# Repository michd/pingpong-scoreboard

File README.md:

# Pingpong Scoreboard

This is an electronics hardware and firmware project for a Pingpong scoreboard.

Its user interface consists for a 4-digit 7 segment display, a few LEDs, a button for each side of the table, and a button for the scoreboard.

The scoreboard keeps track of the score within the game, within the set (games won each side since power-up) and of the overall score (games won each side, all time).

## Hardware

Since the program for this is really simple, and there isn't much I/O, an ATTiny84 was chose as the microcontroller, of the Microchip/AVR range. It is programmed via ISP, and I'm programming it using a Waveshare AVRISP MKII.

The display is driven using a Maxim Integrated MAX7219. The few extra indication LEDs are also driven by that, since the chip supports up to 8 digits, and the project only requires 4.

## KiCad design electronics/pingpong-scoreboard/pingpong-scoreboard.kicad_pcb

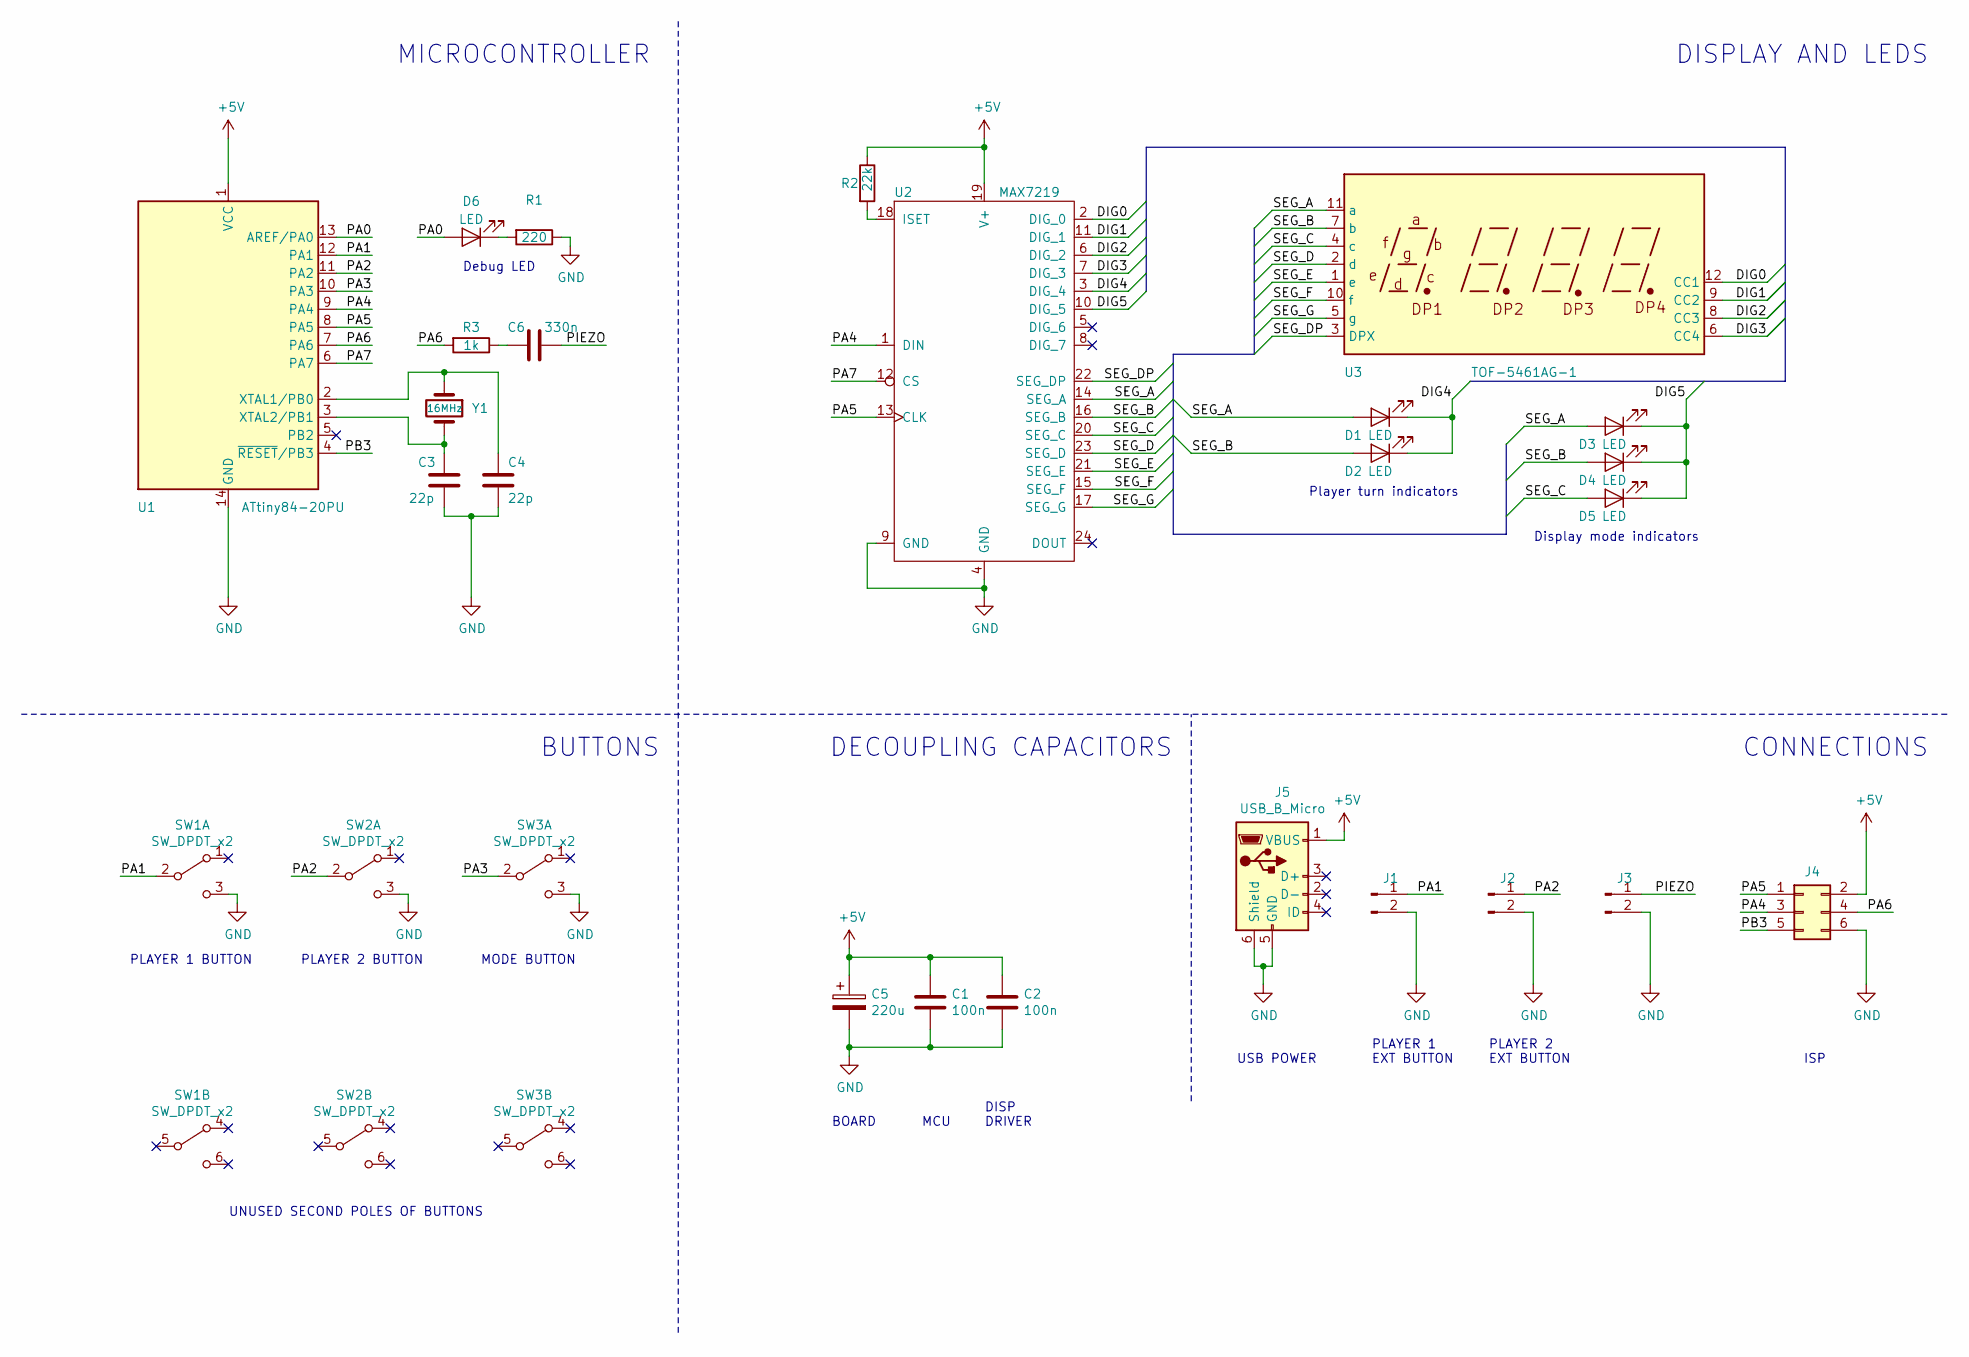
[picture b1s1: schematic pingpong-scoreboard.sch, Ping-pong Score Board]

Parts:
C1, C2: 100n; C_Disc_D4.3mm_W1.9mm_P5.00mm
C3, C4: 22p; C_Disc_D4.3mm_W1.9mm_P5.00mm
C5: 220u; CP_Radial_D6.3mm_P2.50mm
C6: 330n; C_0603_1608Metric
D1, D2: LED; LED_D5.0mm_Clear
D3, D4, D5: LED; LED_D5.0mm
D6: LED; LED_0603_1608Metric
J1, J2, J3: Conn_01x02_Male; PinHeader_1x02_P2.54mm_Horizontal
J4: Conn_02x03_Odd_Even; IDC-Header_2x03_P2.54mm_Horizontal
J5: USB_B_Micro; USB_Micro-B_Amphenol_10103594-0001LF_Horizontal
R1: 220; R_0603_1608Metric
R2: 22k; R_0603_1608Metric
R3: 1k; R_0603_1608Metric
SW1, SW2, SW3: SW_DPDT_x2; 6-pin-momentary-push-button
U1: ATtiny84-20PU; DIP-14_W7.62mm_LongPads
U2: MAX7219; DIP-24_W7.62mm_LongPads
U3: TOF-5461AG-1; CA56-12CGKWA
Y1: 16MHz; Resonator-2Pin_W10.0mm_H5.0mm

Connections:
+5V: C1.1, C2.1, C5.1, J4.2, J5.1 (VBUS), R2.1, U1.1 (VCC), U2.19 (V+)
/DIG0: U2.2 (DIG_0), U3.12 (CC1)
/DIG1: U2.11 (DIG_1), U3.9 (CC2)
/DIG2: U2.6 (DIG_2), U3.8 (CC3)
/DIG3: U2.7 (DIG_3), U3.6 (CC4)
/DIG4: D1.1 (K), D2.1 (K), U2.3 (DIG_4)
/DIG5: D3.1 (K), D4.1 (K), D5.1 (K), U2.10 (DIG_5)
/PA0: D6.2 (A), U1.13 (AREF/PA0)
/PA1: J1.1, SW1.2 (B), U1.12 (PA1)
/PA2: J2.1, SW2.2 (B), U1.11 (PA2)
/PA3: SW3.2 (B), U1.10 (PA3)
/PA4: J4.3, U1.9 (PA4), U2.1 (DIN)
/PA5: J4.1, U1.8 (PA5), U2.13 (CLK)
/PA6: J4.4, R3.2, U1.7 (PA6)
/PA7: U1.6 (PA7), U2.12 (CS)
/PB3: J4.5, U1.4 (~RESET~/PB3)
/PIEZO: C6.1, J3.1
/SEG_A: D1.2 (A), D3.2 (A), U2.14 (SEG_A), U3.11 (a)
/SEG_B: D2.2 (A), D4.2 (A), U2.16 (SEG_B), U3.7 (b)
/SEG_C: D5.2 (A), U2.20 (SEG_C), U3.4 (c)
/SEG_D: U2.23 (SEG_D), U3.2 (d)
/SEG_DP: U2.22 (SEG_DP), U3.3 (DPX)
/SEG_E: U2.21 (SEG_E), U3.1 (e)
/SEG_F: U2.15 (SEG_F), U3.10 (f)
/SEG_G: U2.17 (SEG_G), U3.5 (g)
GND: C1.2, C2.2, C3.2, C4.2, C5.2, J1.2, J2.2, J3.2, J4.6, J5.5 (GND), J5.6 (Shield), R1.1, SW1.3 (C), SW2.3 (C), SW3.3 (C), U1.14 (GND), U2.4 (GND), U2.9 (GND)
unnamed: C3.1, U1.3 (XTAL2/PB1), Y1.2
unnamed: C4.1, U1.2 (XTAL1/PB0), Y1.1
unnamed: C6.2, R3.1
unnamed: D6.1 (K), R1.2
unnamed: R2.2, U2.18 (ISET)

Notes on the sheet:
Player turn indicators
Display mode indicators
PLAYER 1 BUTTON
PLAYER 2 BUTTON
MODE BUTTON
UNUSED SECOND POLES OF BUTTONS
Debug LED
PLAYER 1 EXT BUTTON
PLAYER 2 EXT BUTTON
ISP
USB POWER
CONNECTIONS
BOARD
MCU
DISP DRIVER
DECOUPLING CAPACITORS
BUTTONS
MICROCONTROLLER
DISPLAY AND LEDS

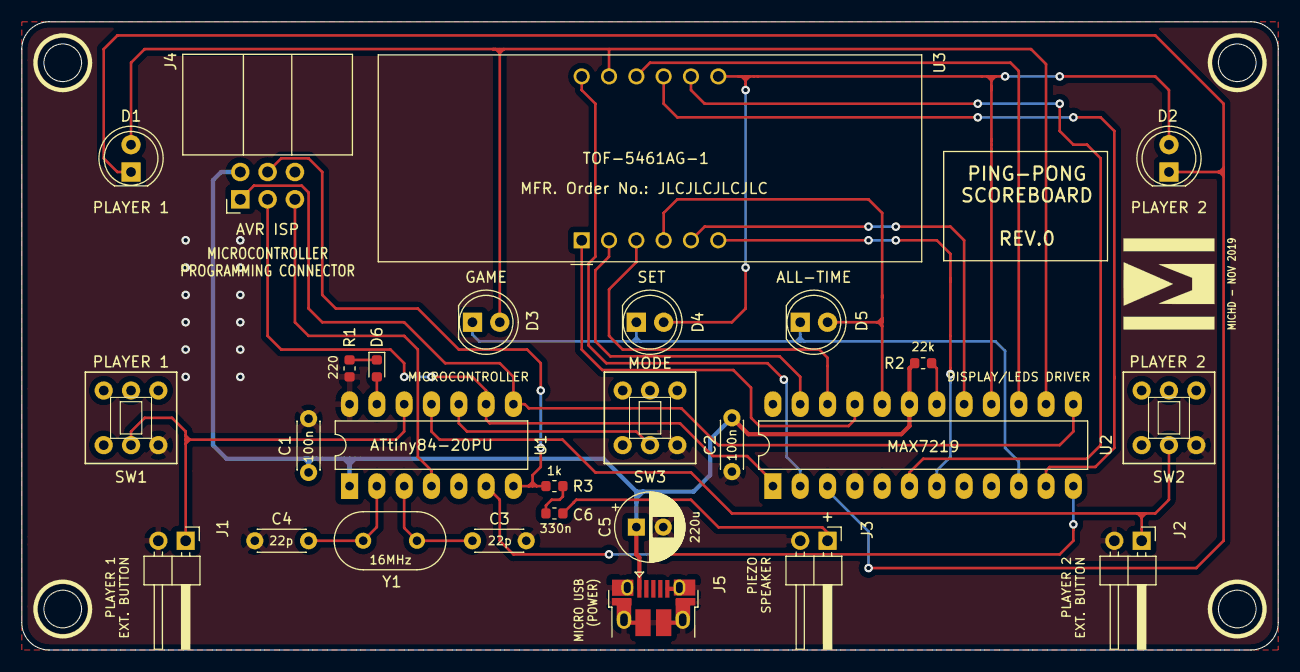
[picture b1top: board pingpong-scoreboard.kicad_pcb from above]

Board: 2 copper layers, 116.8 x 58.4 mm, 27 parts (0 on the bottom side), 31 nets.

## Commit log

2019-11-09 Initial commit: start of firmware (buttons, disp)
    Also starts implementing the actual score-keeping logic, but a lot left
    to do.
2019-11-10 Debounce buttons, implement more game logic
2019-11-10 Add LEDs to indicate what's on the display
2019-11-11 Add saving to EEPROM
2019-11-11 Save alltime score to eeprom w/ delay
2019-11-11 Fix MAX72S19 SetLed method, to use correct digit reg
2019-11-11 Indicate with display dot when alltime score saved
    Just a minor visual indicator to let you know it's okay to power off,
    and be sure the score is saved.
2019-11-11 Preserve EEPROM across flash writes (MakeFile)
2019-11-11 Add characters for "Ping pong" to MAX72S19 decoding
2019-11-11 Add animation system
    Using the main tick interrupts, allows running animation implemented
    with a little bit of data, and frame/finished functions. Supports
    infinite animations too.
    Animations can be used for anything, not just display-related things.
2019-11-11 Add a startup "ping pong" fading animation
    Just 'cause.
2019-11-15 Set up Timer1 for audio out (simple square waves)
    This will be driving a piezo speaker, used for playing a little tune
    when a game ends, and possibly other sound effects.
2019-11-15 Add KiCad schematic
2019-11-15 Lay out PCB components + add piezo output
2019-11-15 Route PCB, set up nice silkscreen
2019-11-16 Add tone generator, allowing actually playing notes
    Note frequencies come out somewhat approximate when leaving the C3-C5
    range, but close enough.
2019-11-16 Remove animation finished callback, pointless
2019-11-16 Move startup, win animation to animation.c
    Also allow clearing animation that is ongoing, which makes it
    immediately execute its final frame.
    Position incrementing in animation is now done by the animation system
    instead of the animation's frame function. Frame functions may still
    manipulate the position, but it's not recommended.
2019-11-16 Put MAX72S19 lib on diet, cut out some cruft
2019-11-16 Add system to play melodies as concurrent animation
    Quite tricky, and had to refactor in favor of size slightly.
2019-11-17 Add win melody + some tweaks in prioritising melodies
2019-11-17 Shorter startup melody
2019-11-17 Increase speed on startup animation
2019-11-23 Add code fix for incorrect display wiring on board
    Oops. The digits were essentially inverted, so now re-assigning them in
    the display driver file instead of bodging the hardware.
2019-11-23 Rewrite button press/long press handling
    This was very buggy, with double presses and wrong buttons being
    triggered. Now seems to work quite reliably without any double or missed
    presses, let alone the display mode occasionally being changed when
    pressing a player button. Still not sure what caused that last one, but
    I'm guessing it's race conditions.
2022-04-09 Firmware: fix some tone generation bug
    (These changes were over a year ago and I'm about to reinstall the OS on
    this computer, just making sure they don't get lost)
